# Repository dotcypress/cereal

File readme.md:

# Cereal

Compact, CP2102N based, USB-C to UART bridge.

## CP2102N Features

- USB 2.0 full-speed compatible
- Data transfer rates up to 3 Mbaud
- Low operating current: 9.5 mA
- Royalty-free Virtual COM port drivers

## Resources

- [Order board on Oshpark](https://oshpark.com/shared_projects/K6b0akiH)(🚨 Important: choose 0.8mm thickness board)
- [Schematics](docs/schematics.pdf)
- [Gerber files](gerber)
- [BOM](docs/bom.csv)

## License

Licensed under either of

- Apache License, Version 2.0 ([LICENSE-APACHE](LICENSE-APACHE) or
  http://www.apache.org/licenses/LICENSE-2.0)
- MIT license ([LICENSE-MIT](LICENSE-MIT) or http://opensource.org/licenses/MIT)

at your option.

### Contribution

Unless you explicitly state otherwise, any contribution intentionally submitted
for inclusion in the work by you, as defined in the Apache-2.0 license, shall be
dual licensed as above, without any additional terms or conditions.

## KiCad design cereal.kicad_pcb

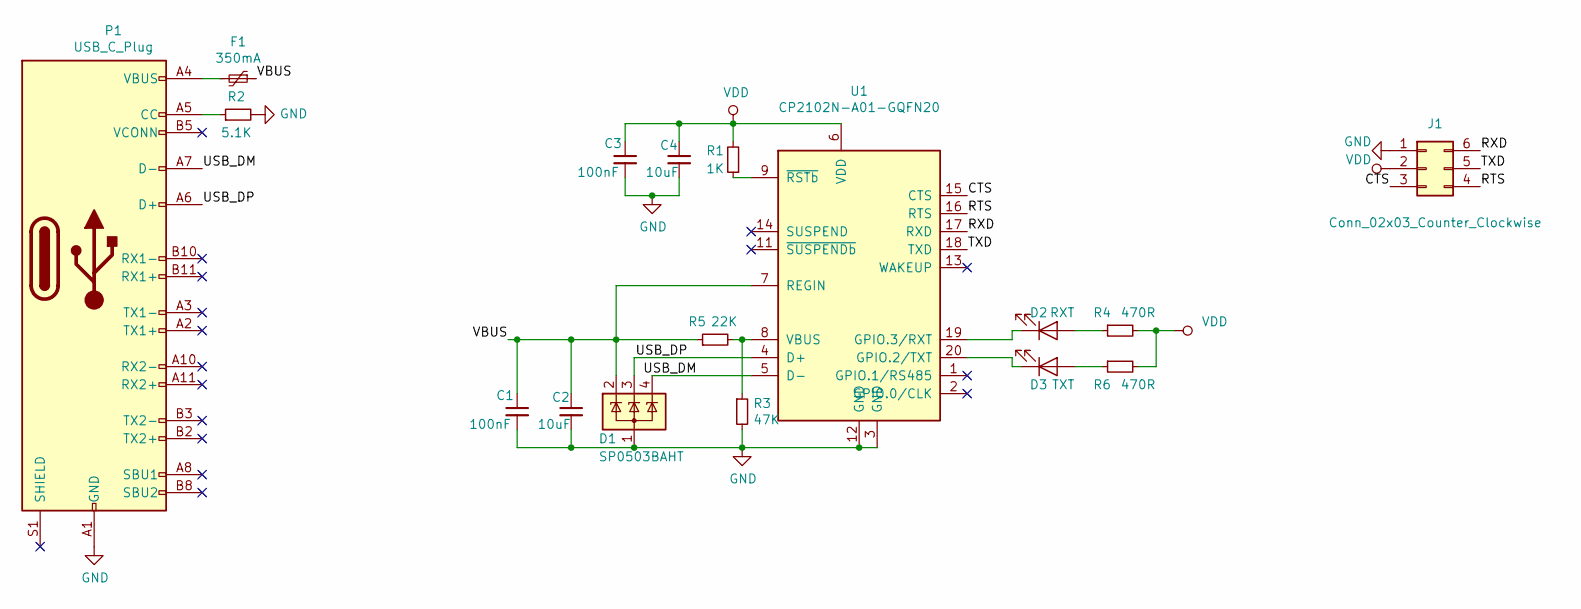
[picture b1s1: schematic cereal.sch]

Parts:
C1, C3: 100nF; C_0603_1608Metric
C2, C4: 10uF; C_0603_1608Metric
D1: SP0503BAHT; SOT-143
D2: RXT; LED_0603_1608Metric
D3: TXT; LED_0603_1608Metric
F1: 350mA; Fuse_0603_1608Metric
J1: Conn_02x03_Counter_Clockwise; PinHeader_2x03_P2.00mm_Vertical
P1: USB_C_Plug; USB_C_Plug_HRS_CX60-24S-UNIT
R1: 1K; R_0603_1608Metric
R2: 5.1K; R_0603_1608Metric
R3: 47K; R_0603_1608Metric
R4, R6: 470R; R_0603_1608Metric
R5: 22K; R_0603_1608Metric
U1: CP2102N-A01-GQFN20; SiliconLabs_QFN-20-1EP_3x3mm_P0.5mm

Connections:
/CTS: J1.3, U1.15 (CTS)
/RTS: J1.4, U1.16 (RTS)
/RXD: J1.6, U1.17 (RXD)
/TXD: J1.5, U1.18 (TXD)
/USB_DM: D1.4 (K), P1.A7 (D-), U1.5 (D-)
/USB_DP: D1.3 (K), P1.A6 (D+), U1.4 (D+)
/VBUS: C1.1, C2.1, D1.2 (K), F1.1, R5.1, U1.7 (REGIN)
GND: C1.2, C2.2, C3.2, C4.2, D1.1 (A), J1.1, P1.A1 (GND), P1.A12 (GND), P1.B1 (GND), P1.B12 (GND), R2.2, R3.2, U1.3 (GND), U1.12 (GND)
unnamed: D2.1 (K), U1.19 (GPIO.3/RXT)
unnamed: D2.2 (A), R4.1
unnamed: D3.1 (K), U1.20 (GPIO.2/TXT)
unnamed: D3.2 (A), R6.1
unnamed: F1.2, P1.A4 (VBUS), P1.A9 (VBUS), P1.B4 (VBUS), P1.B9 (VBUS)
unnamed: P1.A5 (CC), R2.1
unnamed: R1.1, U1.9 (~RSTb)
unnamed: R3.1, R5.2, U1.8 (VBUS)
VDD: C3.1, C4.1, J1.2, R1.2, R4.2, R6.2, U1.6 (VDD)

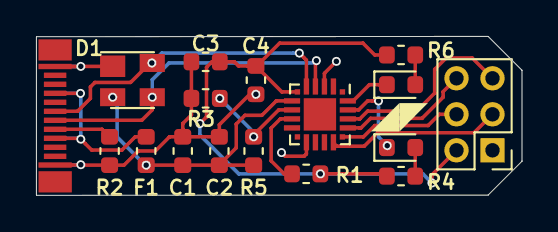
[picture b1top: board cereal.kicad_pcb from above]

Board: 2 copper layers, 27.0 x 8.8 mm, 17 parts (0 on the bottom side), 17 nets.

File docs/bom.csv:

Reference, Value, Footprint, Datasheet
"P1","USB_C_Plug","cereal:USB_C_Plug_HRS_CX60-24S-UNIT","https://www.digikey.com/product-detail/en/hirose-electric-co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"
"D1","SP0503BAHT","Package_TO_SOT_SMD:SOT-143","http://www.littelfuse.com/~/media/files/littelfuse/technical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"
"R1","1K","Resistor_SMD:R_0603_1608Metric","~"
"R3","47K","Resistor_SMD:R_0603_1608Metric","~"
"R4","470R","Resistor_SMD:R_0603_1608Metric","~"
"D2","RXT","LED_SMD:LED_0603_1608Metric","~"
"C2","10uF","Capacitor_SMD:C_0603_1608Metric","~"
"C1","100nF","Capacitor_SMD:C_0603_1608Metric","~"
"R2","5.1K","Resistor_SMD:R_0603_1608Metric","~"
"R5","22K","Resistor_SMD:R_0603_1608Metric","~"
"U1","CP2102N-A01-GQFN20","Package_DFN_QFN:SiliconLabs_QFN-20-1EP_3x3mm_P0.5mm","https://www.silabs.com/documents/public/data-sheets/cp2102n-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"
"C4","10uF","Capacitor_SMD:C_0603_1608Metric","~"
"C3","100nF","Capacitor_SMD:C_0603_1608Metric","~"
"R6","470R","Resistor_SMD:R_0603_1608Metric","~"
"D3","TXT","LED_SMD:LED_0603_1608Metric","~"
"J1","Conn_02x03_Counter_Clockwise","Connector_PinHeader_2.00mm:PinHeader_2x03_P2.00mm_Vertical","~"
"F1","350mA","Fuse:Fuse_0603_1608Metric","~"

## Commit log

2020-09-15 rev 0.3
